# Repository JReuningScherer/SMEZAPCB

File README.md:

# Team Solar - SMEZA PCB Repository

This is the repository for the PCB for the SMEZA. 

Code for the SMEZA should not be stored here - put those files in the [Team-Solar](https://github.com/kyperrone/Team-Solar) repo. 

We are using KiCad 7 for this project, as well as the following extensions:
- Freerouting extension, provided by the Official KiCad Repository. 
- Bounti's JLCPCB extension. This is in a [separate repository](https://github.com/Bouni/kicad-jlcpcb-tools) that must be added. 

# Explaination of Contents 
`smeza_pcb` - This folder contains the KiCad project files for the SMEZA PCB. 

`footprints` - This folder contains all of the project specific footprints in a convenient location. The footprint names in this folder are less than useful, so there is a README file that indicates which file is for which component. 

`symbols` - This folder contains all of the project specific symbols and footprints. Each component has its own folder. 

# Getting Started with using this repo 
I don't know how familiar everyone is with Git so I'm going to say a few things that are probably obvious to more experienced users. 

The primary branch for this repo is `main`. 

Please don't commit directly to main; make a branch for your changes and then when you are done make a pull-request. 

When possible, it is preferred that you obtain this repo by cloning it. However, since most Valpo machines do not have git it may be necessary to download the files and then try to merge after the fact. This is another good time to use a branch incase things get messed up. It should be noted that the 4-machines in the team solar senior design space have git installed - just make sure to use the git-bash terminal. 

While the KiCad files are technically text files, because of the large scale of changes made by even small changes, best practice is probably to clobber everything in `main` with the contents of the newer branch. 

If you have questions about using git, talk to Joel.

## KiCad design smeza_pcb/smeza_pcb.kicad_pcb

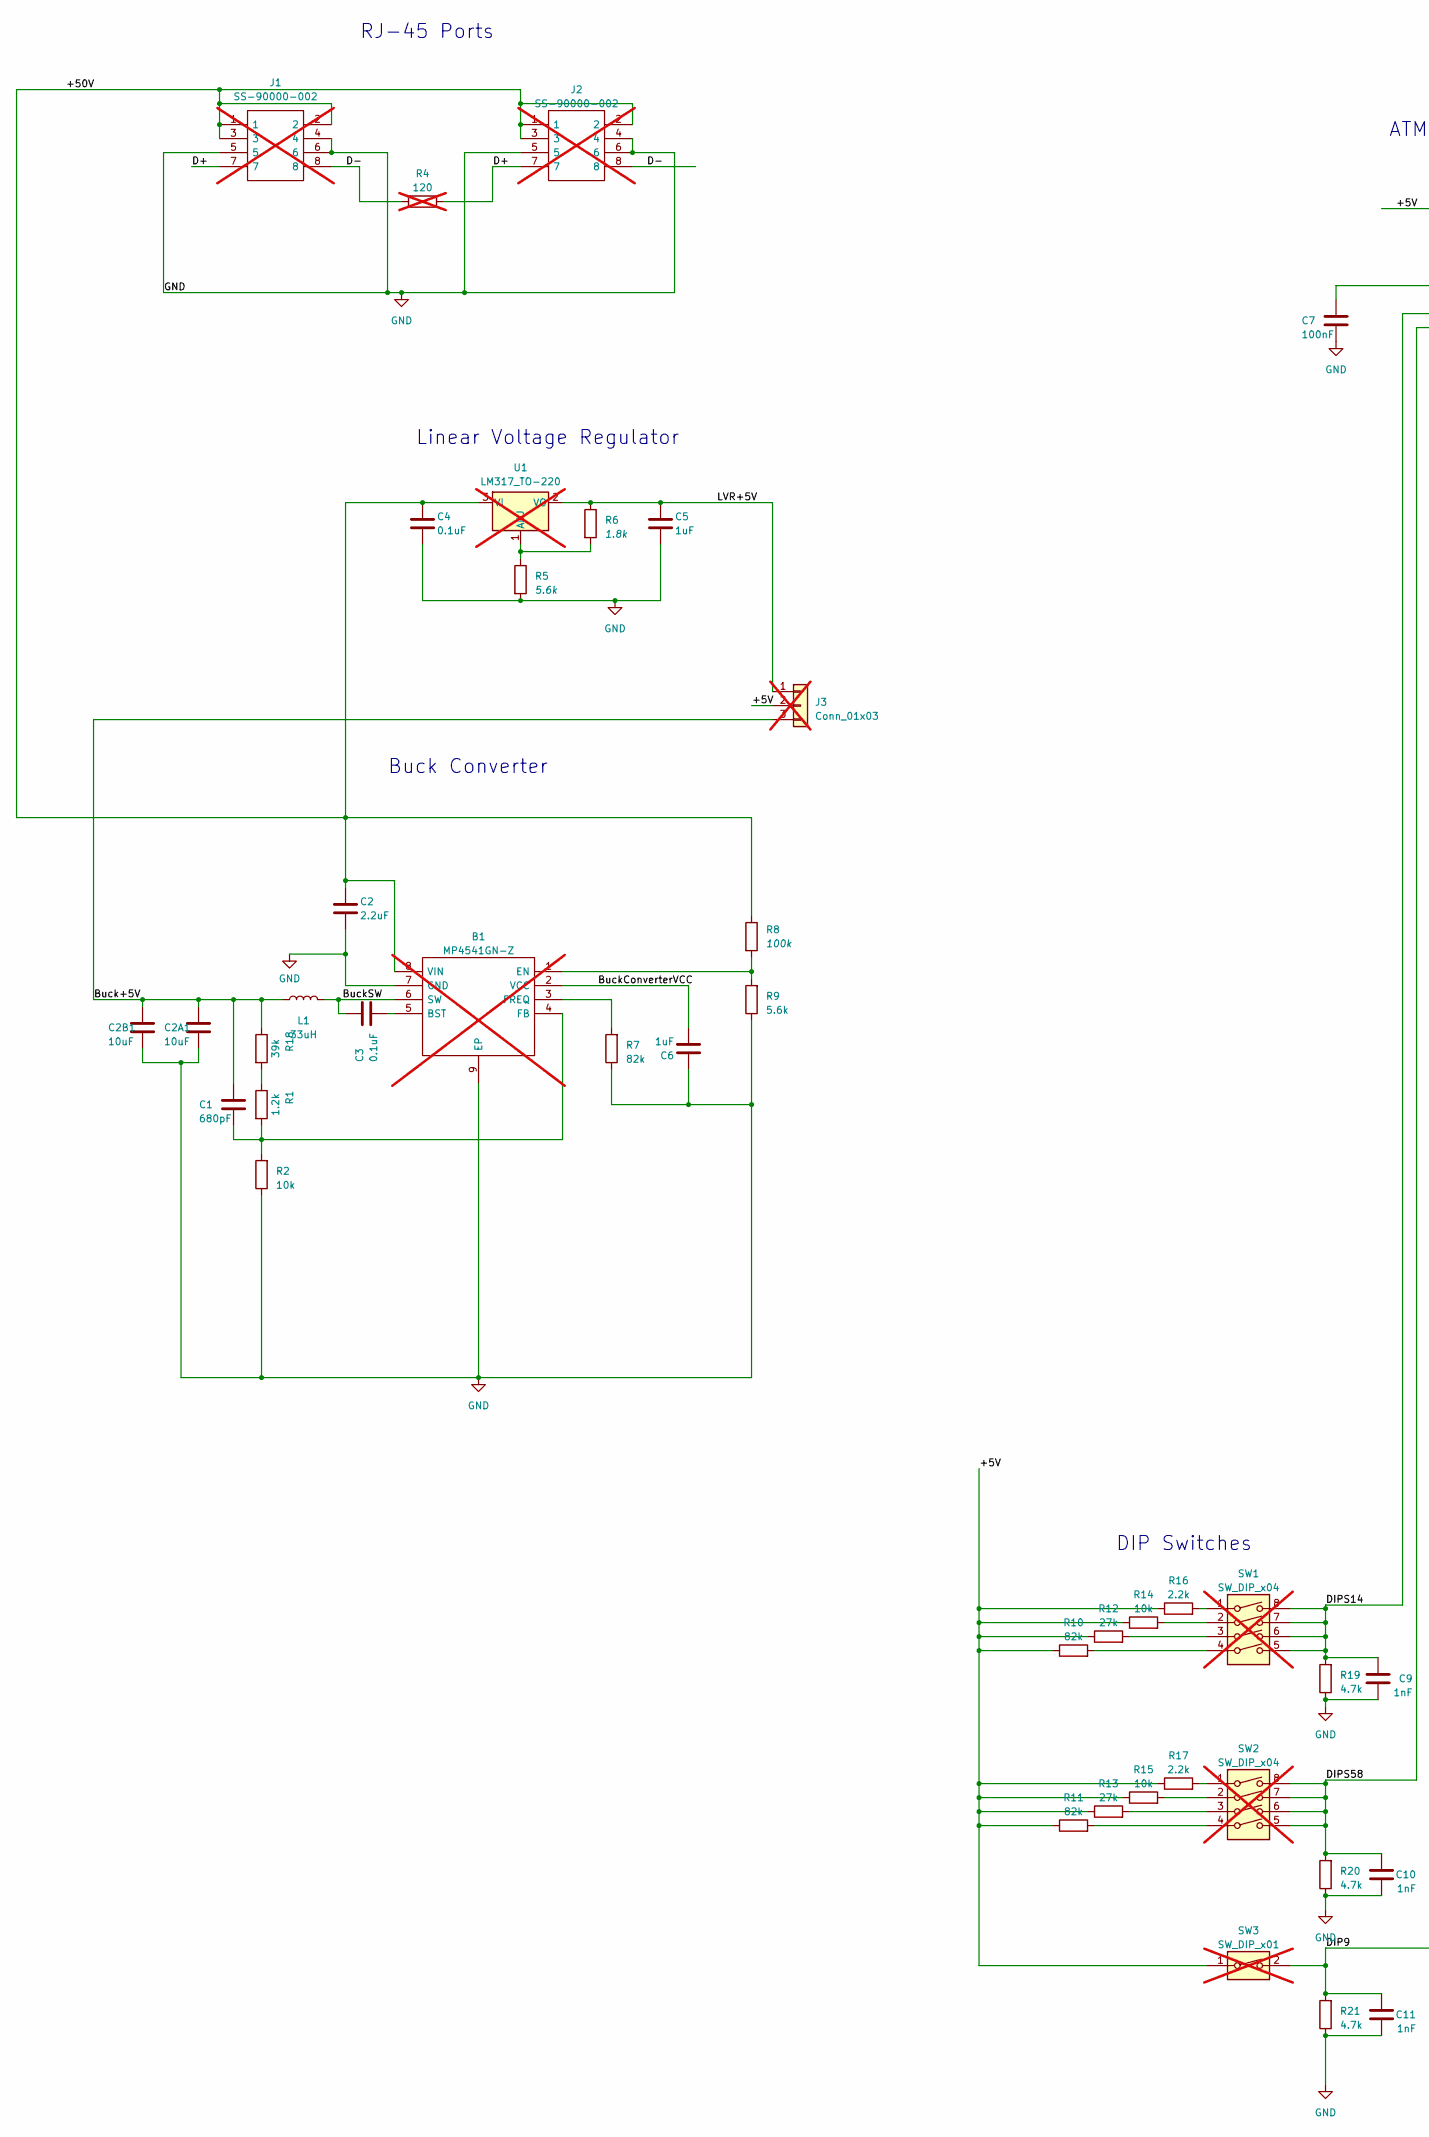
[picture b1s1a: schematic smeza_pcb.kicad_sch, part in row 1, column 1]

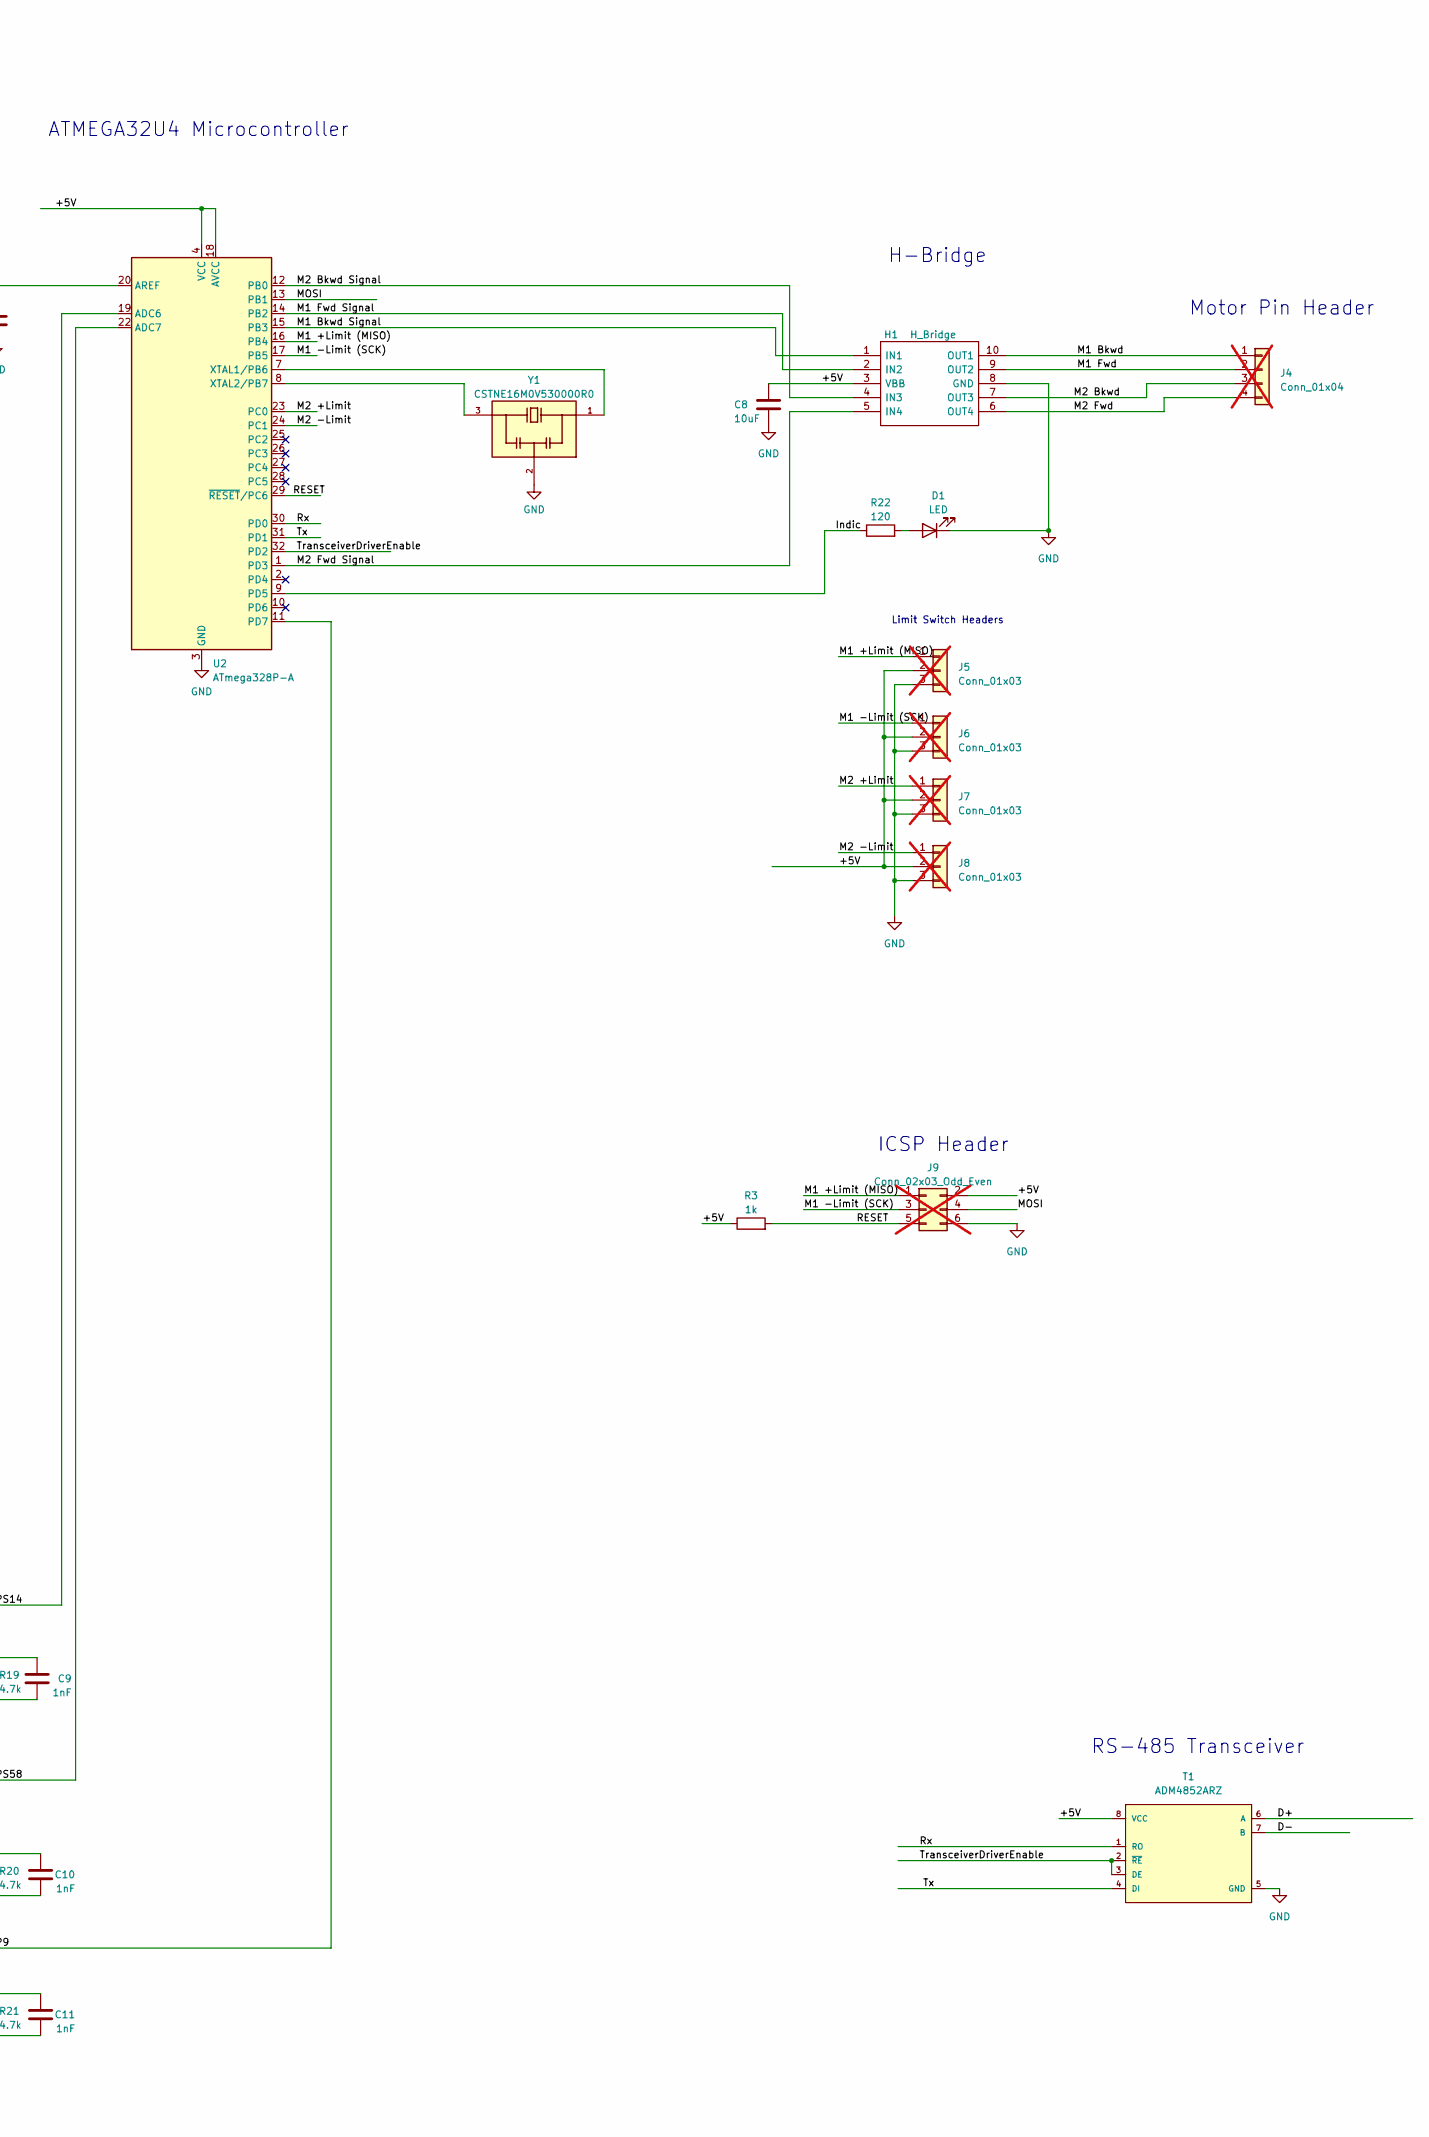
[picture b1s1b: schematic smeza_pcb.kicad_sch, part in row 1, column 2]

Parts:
B1: MP4541GN-Z; SOIC127P600X170-9N; Mouser Part Number 946-MP4541GN-Z; not fitted
C1: 680pF; C_0603_1608Metric
C2: 2.2uF; C_1206_3216Metric
C2A1, C2B1, C8: 10uF; C_1206_3216Metric
C3, C4: 0.1uF; C_1206_3216Metric
C5, C6: 1uF; C_1206_3216Metric
C7: 100nF; C_1206_3216Metric
C9, C10, C11: 1nF; C_1206_3216Metric
D1: LED; LED_0603_1608Metric
H1: H_Bridge; SOIC100P600X175-10N; Manufacturer_Part_Number A3909GLNTR-T; Mouser Part Number 250-A3909GLNTR-T
J1, J2: SS-90000-002; SS90000002; Mouser Part Number 530-SS-90000-002; not fitted
J3: Conn_01x03; PinHeader_1x03_P2.54mm_Vertical; not fitted
J4: Conn_01x04; Molex_KK-254_AE-6410-04A_1x04_P2.54mm_Vertical; not fitted
J5, J6, J7, J8: Conn_01x03; Molex_KK-254_AE-6410-03A_1x03_P2.54mm_Vertical; not fitted
J9: Conn_02x03_Odd_Even; PinHeader_2x03_P2.54mm_Vertical; not fitted
L1: 33uH; L_Taiyo-Yuden_NR-60xx_HandSoldering
R1: 1.2k; R_0805_2012Metric
R2, R14, R15: 10k; R_0805_2012Metric
R3: 1k; R_1206_3216Metric
R4: 120; R_0805_2012Metric; not fitted
R5, R9: 5.6k; R_0805_2012Metric
R6: 1.8k; R_0805_2012Metric
R7, R10, R11: 82k; R_0805_2012Metric
R8: 100k; R_0805_2012Metric
R12, R13: 27k; R_0805_2012Metric
R16, R17: 2.2k; R_0805_2012Metric
R18: 39k; R_0805_2012Metric
R19, R20, R21: 4.7k; R_0805_2012Metric
R22: 120; R_0805_2012Metric
SW1, SW2: SW_DIP_x04; SW_DIP_SPSTx04_Slide_9.78x12.34mm_W7.62mm_P2.54mm; not fitted
SW3: SW_DIP_x01; SW_DIP_SPSTx01_Slide_9.78x4.72mm_W7.62mm_P2.54mm; not fitted
T1: ADM4852ARZ; mouser part number 584-ADM4852ARZ; digikey description IC TRANSCEIVER HALF 1/1 8SOIC
U1: LM317_TO-220; TO-220-3_Vertical; not fitted
U2: ATmega328P-A; TQFP-32_7x7mm_P0.8mm
Y1: CSTNE16M0V530000R0; OSC_CSTNE16M0V530000R0; PARTREV JGC42-8853B

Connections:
/+5V: C8.1, H1.3 (VBB), J3.2, J5.2, J6.2, J7.2, J8.2, J9.2, R3.1, R10.1, R11.1, R12.1, R13.1, R14.1, R15.1, R16.1, R17.1, SW3.1, T1.8 (VCC), U2.4 (VCC), U2.6 (VCC), U2.18 (AVCC)
/+50V: B1.8 (VIN), C2.1, C4.1, J1.1, J1.2, J1.3, J2.1, J2.2, J2.3, R8.1, U1.3 (VI)
/Buck+5V: C1.1, C2A1.1, C2B1.1, J3.3, L1.1, R18.1
/BuckConverterVCC: B1.2 (VCC), C6.2
/BuckSW: B1.6 (SW), C3.1, L1.2
/D+: J1.7, J2.7, R4.1, T1.6 (A)
/D-: J1.8, J2.8, R4.2, T1.7 (B)
/DIP9: C11.1, R21.2, SW3.2, U2.11 (PD7)
/DIPS14: C9.1, R19.2, SW1.5, SW1.6, SW1.7, SW1.8, U2.19 (ADC6)
/DIPS58: C10.1, R20.2, SW2.5, SW2.6, SW2.7, SW2.8, U2.22 (ADC7)
/Indic: R22.1, U2.9 (PD5)
/LVR+5V: C5.1, J3.1, R6.1, U1.2 (VO)
/M1 +Limit (MISO): J5.1, J9.1, U2.16 (PB4)
/M1 -Limit (SCK): J6.1, J9.3, U2.17 (PB5)
/M1 Bkwd: H1.10 (OUT1), J4.1
/M1 Bkwd Signal: H1.1 (IN1), U2.15 (PB3)
/M1 Fwd: H1.9 (OUT2), J4.2
/M1 Fwd Signal: H1.2 (IN2), U2.14 (PB2)
/M2 +Limit: J7.1, U2.23 (PC0)
/M2 -Limit: J8.1, U2.24 (PC1)
/M2 Bkwd: H1.7 (OUT3), J4.3
/M2 Fwd: H1.6 (OUT4), J4.4
/M2 Fwd Signal: H1.5 (IN4), U2.1 (PD3)
/RESET: J9.5, R3.2, U2.29 (~RESET/PC6)
/Rx: T1.1 (RO), U2.30 (PD0)
/TransceiverDriverEnable: T1.2 (~RE), T1.3 (DE), U2.32 (PD2)
/Tx: T1.4 (DI), U2.31 (PD1)
GND: B1.7 (GND), B1.9 (EP), C2.2, C2A1.2, C2B1.2, C4.2, C5.2, C6.1, C7.2, C8.2, C9.2, C10.2, C11.2, D1.1 (K), H1.8 (GND), J1.4, J1.5, J1.6, J2.4, J2.5, J2.6, J5.3, J6.3, J7.3, J8.3, J9.6, R2.1, R5.2, R7.1, R9.1, R19.1, R20.1, R21.1, T1.5 (GND), U2.3 (GND), U2.5 (GND), U2.21 (GND), Y1.2
unnamed: B1.5 (BST), C3.2
unnamed: B1.1 (EN), R8.2, R9.2
unnamed: B1.4 (FB), C1.2, R1.2, R2.2
unnamed: B1.3 (FREQ), R7.2
unnamed: D1.2 (A), R22.2
unnamed: R1.1, R18.2
unnamed: R10.2, SW1.4
unnamed: R11.2, SW2.4
unnamed: R12.2, SW1.3
unnamed: R13.2, SW2.3
unnamed: R14.2, SW1.2
unnamed: R15.2, SW2.2
unnamed: R16.2, SW1.1
unnamed: R17.2, SW2.1
unnamed: R5.1, R6.2, U1.1 (ADJ)
unnamed: C7.1, U2.20 (AREF)
unnamed: U2.7 (XTAL1/PB6), Y1.1
unnamed: U2.8 (XTAL2/PB7), Y1.3

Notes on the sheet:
H-Bridge
DIP Switches
Buck Converter
ATMEGA32U4 Microcontroller
ICSP Header
Motor Pin Header
RS-485 Transceiver
RJ-45 Ports
Limit Switch Headers
Linear Voltage Regulator

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
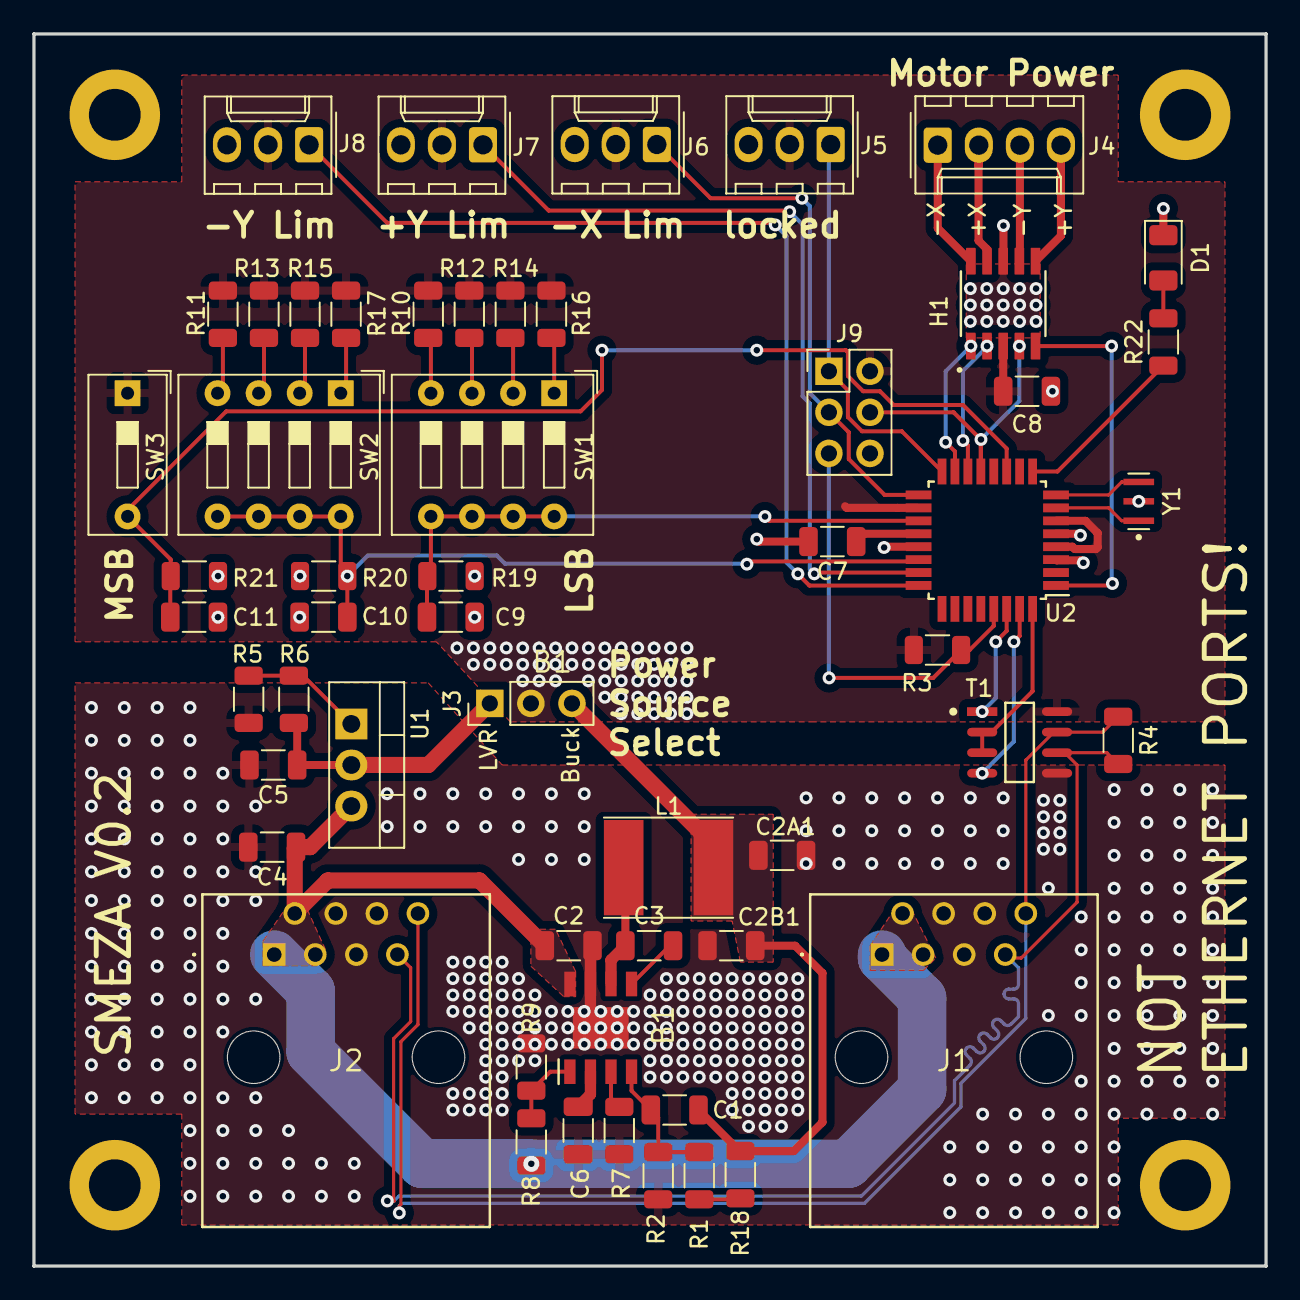
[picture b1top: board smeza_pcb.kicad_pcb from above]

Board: 2 copper layers, 76.2 x 76.2 mm, 55 parts (0 on the bottom side), 47 nets.

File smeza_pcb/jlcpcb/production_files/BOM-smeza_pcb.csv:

Comment,Designator,Footprint,LCSC
10uF,"C2A1,C2B1,C8",C_1206_3216Metric,C13585
ATmega328P-A,U2,TQFP-32_7x7mm_P0.8mm,C14877
100k,R8,R_0805_2012Metric,C149504
680pF,C1,C_0603_1608Metric,C1630
1.2k,R1,R_0805_2012Metric,C17379
1.8k,R6,R_0805_2012Metric,C17398
10k,"R14,R15,R2",R_0805_2012Metric,C17414
120,"R22,R4",R_0805_2012Metric,C17437
2.2k,"R16,R17",R_0805_2012Metric,C17520
27k,"R12,R13",R_0805_2012Metric,C17593
4.7k,"R19,R20,R21",R_0805_2012Metric,C17673
82k,"R10,R11,R7",R_0805_2012Metric,C17840
1uF,"C5,C6",C_1206_3216Metric,C1848
33uH,L1,L_Taiyo-Yuden_NR-60xx_HandSoldering,C2049900
LED,D1,LED_0603_1608Metric,C2286
0.1uF,"C3,C4,C7",C_1206_3216Metric,C24497
39k,R18,R_0805_2012Metric,C25826
H_Bridge,H1,SOIC100P600X175-10N,C2653462
CSTNE16M0V530000R0,Y1,OSC_CSTNE16M0V530000R0,C341521
5.6k,"R5,R9",R_0805_2012Metric,C4382
1k,R3,R_1206_3216Metric,C4410
2.2uF,C2,C_1206_3216Metric,C50254
ADM4852ARZ,T1,ADM4852ARZ,C658245
1nF,"C10,C11,C9",C_1206_3216Metric,C9196
MP4541GN-Z,B1,SOIC127P600X170-9N,

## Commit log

2023-02-22 Initial Commit. Added KiCad Files, Footprints, Symbols.
2023-02-22 Actually added KiCad, Footprints, Symbols. Forgot to stage changes.
2023-02-23 Changed library paths from absolute paths to relative paths. Attempted to fix issue referencing old versions of the schematic.
2023-02-23 Fixed formatting in README
2023-02-24 Corrected Footprints in Schematic. Reorganized passives supporting the buck converter. Rerouted 50V passthough, D+/- passthrough.
2023-02-24 Clarified which extensions we are using. Added a note on merging. Added note on Git usage on Valpo Machines.
2023-02-24 Added note on Git usage.
2023-03-07 Reorganized all components and rerouted. Added capacitors to H-Bridge. Added Capacitors to dip switches. Updated DIP switch footprint. Fixed DRC and ERC errors.
2023-03-07 Resized traces for SW2.
2023-03-07 Finalized LCSC Part Numbers
2023-03-07 Footprint and Symbol Updates
2023-03-07 Included Output Files
2023-03-07 Added Backups
2023-03-11 Moved vias out from under pads
2023-03-11 Updated version text on board
2023-03-11 Separated MOSI and M2 Bkwd pins
2023-03-11 Replaced most extended parts. Swapped out many 1206 resistors for 0805 resistors. Swapped out C1. Swapped out LED. Made all headers DNP. Rerouted to reflect the new footprints.
2023-03-11 Added tooling holes
2023-03-11 Added fiducials and checked component spacing. Removed old JLCPCB files
2023-03-11 Fixed part rotations. Fixed silkscreen goofs. Added solder jumpers.
2023-03-11 Final JCLPCB files Update. Add latest backup
